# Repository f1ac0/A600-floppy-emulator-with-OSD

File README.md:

# Floppy emulator with OSD and selector for the Amiga 600
This is a fusion of a "Gotek" and a "Bluepill" that can provide both FlashFloppy and FF_OSD and also my Amiga-dual-floppy-selector on a single tiny board that fits inside the Amiga 600, under the original floppy drive. Thank you to Keir Fraser for his firmware https://github.com/keirf/FlashFloppy, and to the chinese people for the original device.

Thanks to the OSD and Amiga keyboard support, LCD/OLED display or buttons are no longer necessary and the device can be almost completely hidden inside Amiga computers, without damaging their case. It is still possible to install a display and buttons, though.

In addition, thanks to "Amiga dual floppy selector" feature, it can daisy-chain between the original floppy drive and the motherboard. In this configuration, the OSD let you choose dynamically which drive is DF0 and DF1. You can enjoy both your original games on floppies and disk images on USB or SDcard !

# Disclaimer
This is a hobbyist project, it comes with no warranty and no support. Also remember that the Amiga machines are about 30 years old and may fail because of such hardware expansions.

This version is not endorsed by the author of FlashFloppy, please don't bother him with issues you might have because of it.

I publish my work under the CC-BY-NC-SA license. The content of this repository is the result of weeks of work, requiring investment in tools, parts, prototypes, and risky tests on his own equipment. For this reason the author does not want third parties to sell products and keep all the profit, usually without even offering support to their customers. If you see people selling this without the consent of the author, don't buy from them.

My modifications to the FF_OSD source are under "the unlicense", like the original code.

If you find it useful and want to reward me : I am always looking for Amiga/Amstrad CPC hardware to repair and hack, please contact me.

# BOM
See iBom.

Other boards you may use with it:
- [A600-1200KeyboardSocket](https://github.com/f1ac0/Breakout-and-simple-connector-boards) to pick the keyboard signals on an A600 or A1200
- [USB_A or microSD breakout](https://github.com/f1ac0/Breakout-and-simple-connector-boards) to make the flash memory accessible from outside the system

# Making it
Components are SMD, and have quite thin pin pitch. You need to know what you are doing.

You may choose to install the USB on a remote board, to make them accessible through trapdoors or openings in the case. You may solder buttons, rotary encoder, LED, display and piezo transducer directly : most "pin headers" pads should not be fitted with headers otherwise it will prevent installing the floppy drive over it.

Solder the bottom floppy pin header at the same angle as the drive is installed in the A600. This way the board should be over the back connectors, and the floppy drive connector will fit tightly under the drive. If any doubt, try to install it before soldering.

Check for shorts at least between 5V, 12V and GND traces before applying power ! If it doesn't work after manual soldering, check that all pads are attached and not shorted, good luck!

The programming ports do not need to be soldered since it needs to be programmed just once : you can just hold it in place during the few seconds required for programming.

On the software side, you need to compile FF\_OSD from source, with the small modifications proposed in the "Floppy-emulator-with-OSD" repository. Use `patch -ru -d FF_OSD-master  < patch` to apply them. FlashFloppy does not require any modification.

To program the F103 uC then the F105 uC, I personally use a STLINK clone dongle with the stlink tool : https://github.com/stlink-org/stlink. Each uC has its own SWDIO/SWDCLK pins.

To connect the wires to DRES, MTRX, CSYNC and VIDEO signals on the A600 motherboard without soldering on it, here is a tip:
- Take a metal pin from the female 2.54mm pin socket, which is shaped as a lyre. The one you removed from pin 3 for example.
- Solder the wire on the pin, where you normally solder it.
- Place the pin inside heat-shrink tube, with only 1mm of metal uncovered from the tips of the lyre.
- Snap the tip on the lyre on the inside of the back connector where you need to connect. DRES, MTRX, CSYNC and VIDEO are easily available on the top row of the video and floppy connectors, which is accessible from inside the case!

# Using it
- Plug the floppy ribbon cable on the device ; connect the DRES and MTRX wires on the rear floppy connector ; plug the device on the motherboard floppy connector ; plug the keyboard adapter on U7 (not U13!) ; connect the VIDEO and CSYNC wires on the video connector ; plug the power connectors to the motherboard and to the drive ; Reinstall the drive over it ; manage the USB connector, for axample in place of the modulator.
- Insert the USB thumb drive.
- Turn on the Amiga, enjoy.

To change the drives configuration :
- First you should eject all floppies to prevent confusion of the OS.
- Go to the FF_OSD config menu, change the Drive config setting accordingly. Then Use or Save the new settings.
- If you changed from one to two or two to one drive, then you need to reboot OS for the second drive to be identified or ignored correctly.

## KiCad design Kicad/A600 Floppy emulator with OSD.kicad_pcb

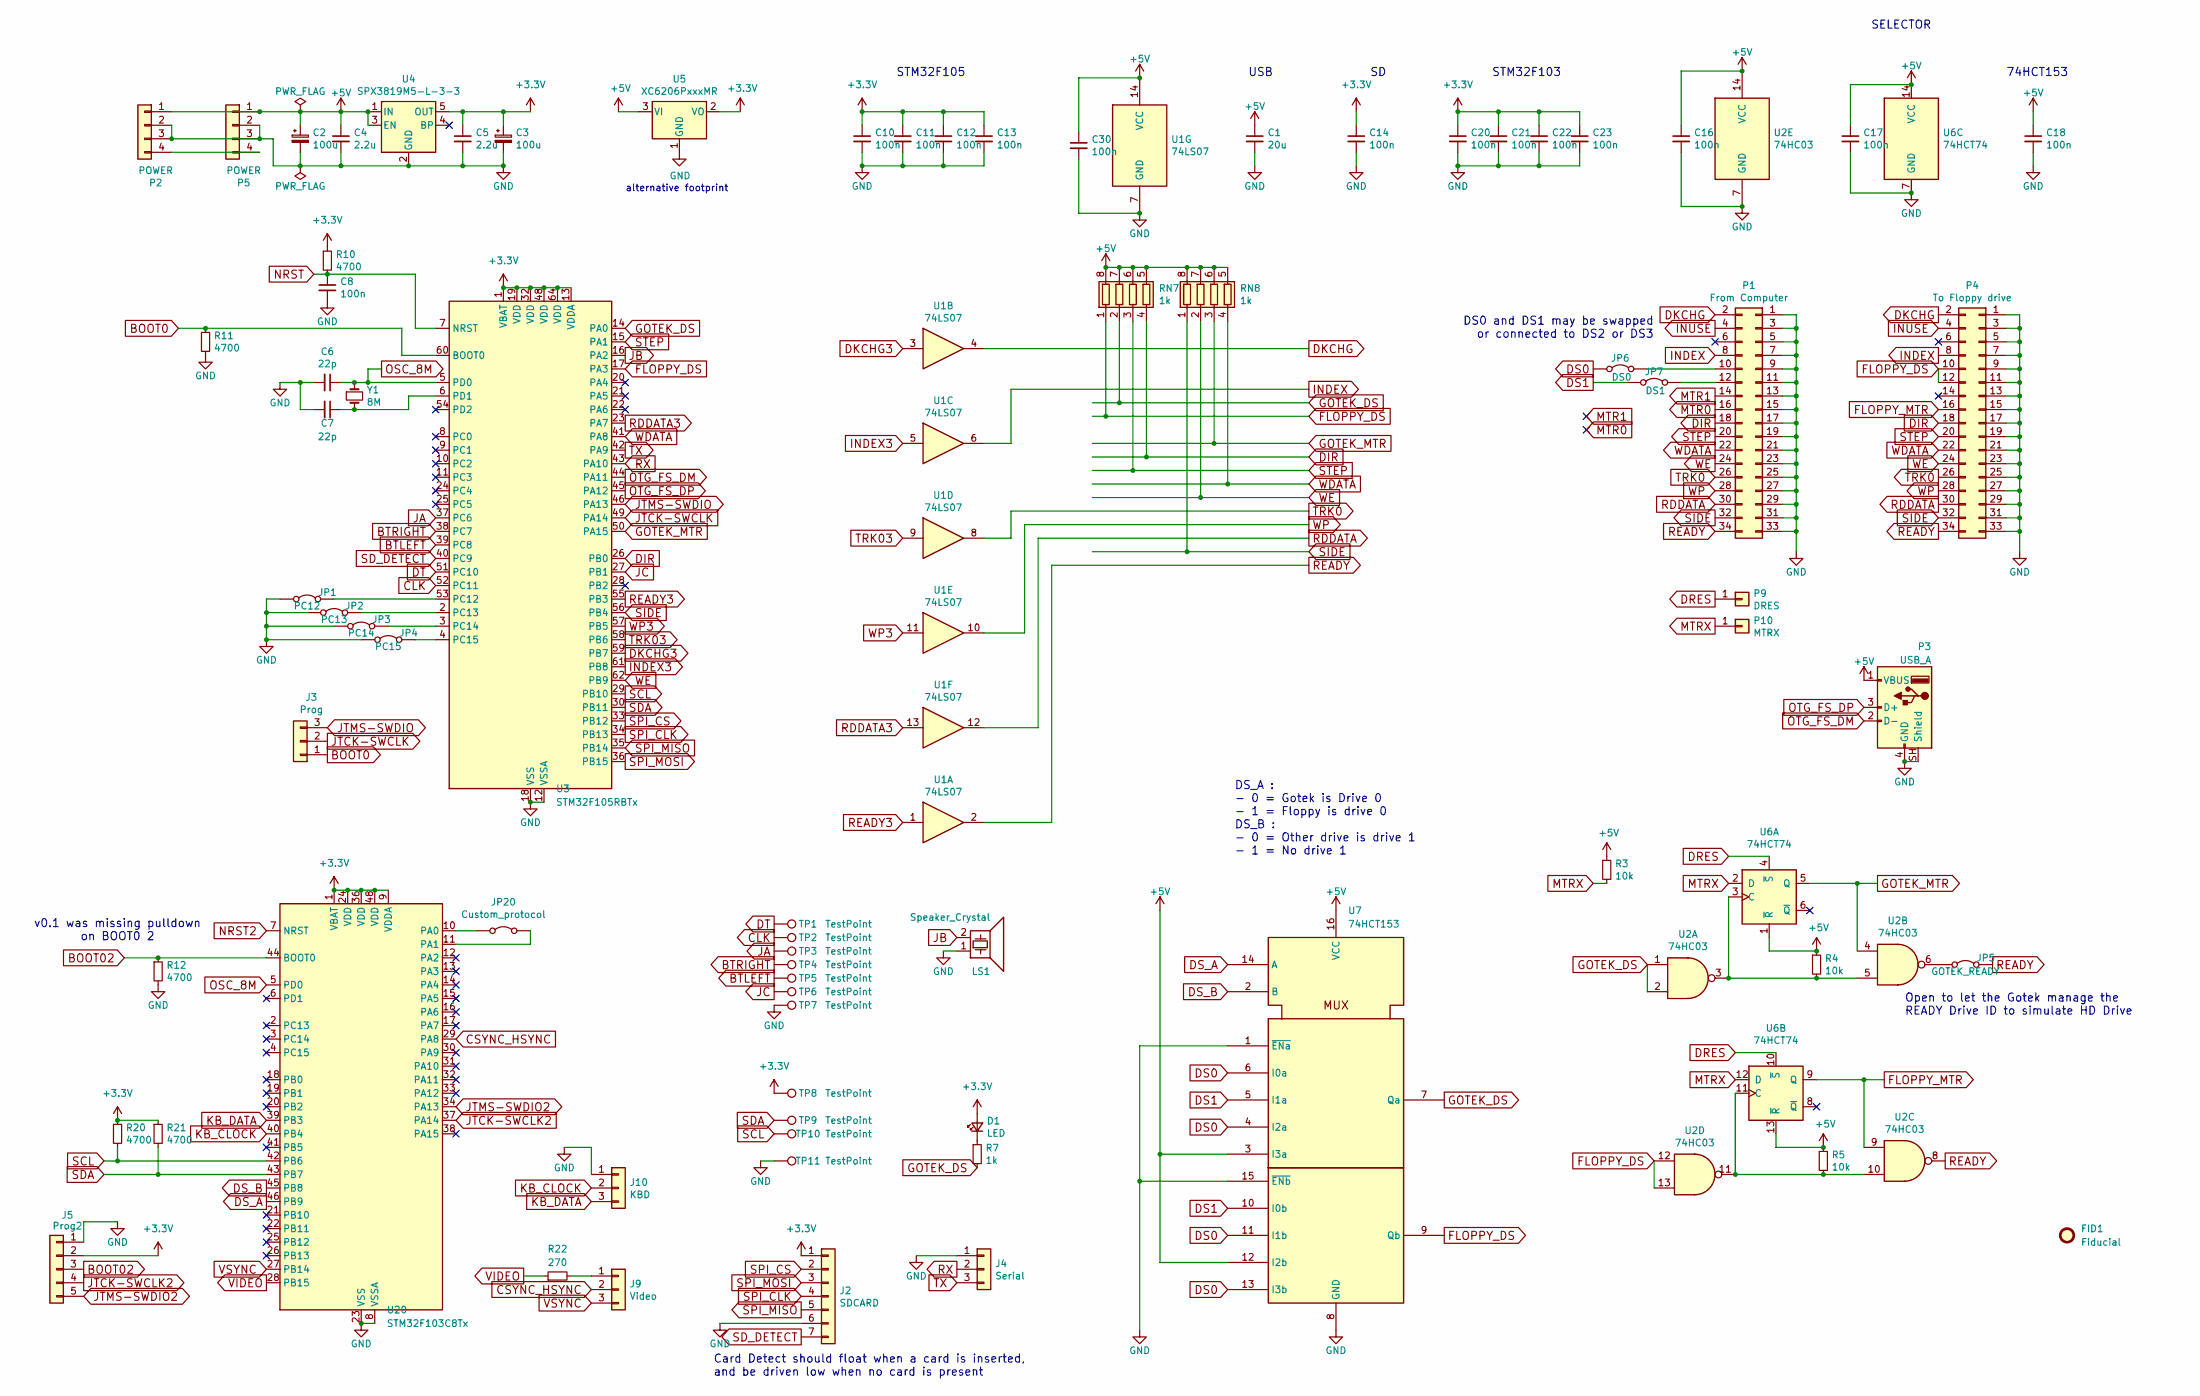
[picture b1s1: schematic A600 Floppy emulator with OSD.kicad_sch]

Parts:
C1: 20u; C_0805_2012Metric
C2, C3: 100u; CP_Radial_D5.0mm_P2.50mm
C4, C5: 2.2u; C_0805_2012Metric
C6, C7: 22p; C_0805_2012Metric
C8, C10, C11, C12, C13, C14, C16, C17, C18, C20, C21, C22, C23, C30: 100n; C_0805_2012Metric
D1: LED; PinHeader_1x02_P2.54mm_Vertical
FID1: Fiducial; CC_BY_NC_SA_long_silkscreen
J2: SDCARD; PinHeader_1x07_P2.54mm_Vertical
J3: Prog; PinHeader_1x03_P2.54mm_Vertical
J4: Serial; PinHeader_1x03_P2.54mm_Vertical
J5: Prog2; PinHeader_1x05_P2.54mm_Vertical
J9: Video; PinHeader_1x03_P2.54mm_Vertical
J10: KBD; PinHeader_1x03_P2.54mm_Vertical
JP1: PC12; SolderJumper-2_P1.3mm_Bridged_RoundedPad1.0x1.5mm
JP2: PC13; SolderJumper-2_P1.3mm_Bridged_RoundedPad1.0x1.5mm
JP3: PC14; SolderJumper-2_P1.3mm_Bridged_RoundedPad1.0x1.5mm
JP4: PC15; SolderJumper-2_P1.3mm_Bridged_RoundedPad1.0x1.5mm
JP5: GOTEK_READY; SolderJumper-2_P1.3mm_Bridged_RoundedPad1.0x1.5mm
JP6: DS0; PinHeader_1x02_P2.54mm_Vertical
JP7: DS1; PinHeader_1x02_P2.54mm_Vertical
JP20: Custom_protocol; SolderJumper-2_P1.3mm_Bridged_RoundedPad1.0x1.5mm
LS1: Speaker_Crystal; PinHeader_1x02_P2.54mm_Vertical
P1: From Computer; PinSocket_2x17_P2.54mm_Vertical
P2: POWER; Floppy_Power_1x04x2.50mm_Horizontal
P3: USB_A; USB_A_female_THT_G54
P4: To Floppy drive; Pin_Header_2x17_Male_EdgeMount_Pitch2.54mm
P5: POWER; Floppy_Power_1x04x2.50mm_Vertical
P9: DRES; PinHeader_1x01_P2.54mm_Vertical
P10: MTRX; PinHeader_1x01_P2.54mm_Vertical
R3, R4, R5: 10k; R_0805_2012Metric
R7: 1k; R_0805_2012Metric
R10, R11, R12, R20, R21: 4700; R_0805_2012Metric
R22: 270; R_0805_2012Metric
RN7, RN8: 1k; R_Array_Convex_4x0603
TP1, TP2, TP3, TP4, TP5, TP6, TP7, TP8, TP9, TP10, TP11: TestPoint; TestPoint_THTPad_D1.7mm_Drill1.0mm
U1: 74LS07; SOIC-14_3.9x8.7mm_P1.27mm
U2: 74HC03; SOIC-14_3.9x8.7mm_P1.27mm
U3: STM32F105RBTx; LQFP-64_10x10mm_P0.5mm
U4: SPX3819M5-L-3-3; SOT-23-5
U5: XC6206PxxxMR; SOT-23
U6: 74HCT74; SOIC-14_3.9x8.7mm_P1.27mm
U7: 74HCT153; SOIC-16_3.9x9.9mm_P1.27mm
U20: STM32F103C8Tx; LQFP-48_7x7mm_P0.5mm
Y1: 8M; Crystal_HC49-4H_Vertical

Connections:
+3.3V: C3.1, C5.1, C10.1, C11.1, C12.1, C13.1, C14.1, C20.1, C21.1, C22.1, C23.1, D1.2 (A), J2.1, J5.2, R10.1, R20.1, R21.1, TP8.1 (1_1), U3.1 (VBAT), U3.13 (VDDA), U3.19 (VDD), U3.32 (VDD), U3.48 (VDD), U3.64 (VDD), U4.5 (OUT), U5.2 (VO), U20.1 (VBAT), U20.9 (VDDA), U20.24 (VDD), U20.36 (VDD), U20.48 (VDD)
+5V: C1.1, C2.1, C4.1, C16.1, C17.1, C18.1, C30.1, P2.1, P3.1 (VBUS), P5.1, R3.1, R4.1, R5.1, RN7.5 (R4.2), RN7.6 (R3.2), RN7.7 (R2.2), RN7.8 (R1.2), RN8.5 (R4.2), RN8.6 (R3.2), RN8.7 (R2.2), RN8.8 (R1.2), U1.14 (VCC), U2.14 (VCC), U4.1 (IN), U4.3 (EN), U5.3 (VI), U6.1 (~R), U6.13 (~R), U6.14 (VCC), U7.3 (I3a), U7.12 (I2b), U7.16 (VCC)
BOOT0: J3.1, R11.1, U3.60 (BOOT0)
BOOT02: J5.3, R12.1, U20.44 (BOOT0)
BTLEFT: TP5.1 (1_1), U3.39 (PC8)
BTRIGHT: TP4.1 (1_1), U3.38 (PC7)
CLK: TP2.1 (1_1), U3.52 (PC11)
CSYNC_HSYNC: J9.2, U20.29 (PA8)
DIR: P1.18, P4.18, RN7.4 (R4.1), U3.26 (PB0)
DKCHG: P1.2, P4.2, U1.4
DKCHG3: U1.3, U3.59 (PB7)
DRES: P9.1 (Pin_1_1), U6.4 (~S), U6.10 (~S)
DS0: JP6.1 (A), U7.4 (I2a), U7.6 (I0a), U7.11 (I1b), U7.13 (I3b)
DS1: JP7.1 (A), U7.5 (I1a), U7.10 (I0b)
DS_A: U7.14 (A), U20.46 (PB9)
DS_B: U7.2 (B), U20.45 (PB8)
DT: TP1.1 (1_1), U3.51 (PC10)
FLOPPY_DS: P4.10, P4.12, RN7.1 (R1.1), U2.12, U2.13, U3.17 (PA3), U7.9 (Qb)
FLOPPY_MTR: P4.16, U2.9, U6.9 (Q)
GND: C1.2, C2.2, C3.2, C4.2, C5.2, C6.2, C7.2, C8.2, C10.2, C11.2, C12.2, C13.2, C14.2, C16.2, C17.2, C18.2, C20.2, C21.2, C22.2, C23.2, C30.2, J2.6, J4.1, J5.1, J10.1, JP1.1 (A), JP2.1 (A), JP3.1 (A), JP4.1 (A), LS1.1, P1.1, P1.3, P1.5, P1.7, P1.9, P1.11, P1.13, P1.15, P1.17, P1.19, P1.21, P1.23, P1.25, P1.27, P1.29, P1.31, P1.33, P2.2, P2.3, P3.4 (GND), P3.SH (Shield), P4.1, P4.3, P4.5, P4.7, P4.9, P4.11, P4.13, P4.15, P4.17, P4.19, P4.21, P4.23, P4.25, P4.27, P4.29, P4.31, P4.33, P5.2, P5.3, R11.2, R12.2, TP7.1 (1_1), TP11.1 (1_1), U1.7 (GND), U2.7 (GND), U3.12 (VSSA), U3.18 (VSS), U3.31 (VSS), U3.47 (VSS), U3.63 (VSS), U4.2 (GND), U5.1 (GND), U6.7 (GND), U7.1 (~ENa), U7.8 (GND), U7.15 (~ENb), U20.8 (VSSA), U20.23 (VSS), U20.35 (VSS), U20.47 (VSS)
GOTEK_DS: R7.2, RN7.2 (R2.1), U2.1, U2.2, U3.14 (PA0), U7.7 (Qa)
GOTEK_MTR: RN8.3 (R3.1), U2.4, U3.50 (PA15), U6.5 (Q)
INDEX: P1.8, P4.8, U1.6
INDEX3: U1.5, U3.61 (PB8)
INUSE: P1.4, P4.4
JA: TP3.1 (1_1), U3.37 (PC6)
JB: LS1.2, U3.16 (PA2)
JC: TP6.1 (1_1), U3.27 (PB1)
JTCK-SWCLK: J3.2, U3.49 (PA14)
JTCK-SWCLK2: J5.4, U20.37 (PA14)
JTMS-SWDIO: J3.3, U3.46 (PA13)
JTMS-SWDIO2: J5.5, U20.34 (PA13)
KB_CLOCK: J10.2, U20.40 (PB4)
KB_DATA: J10.3, U20.39 (PB3)
MTR0: P1.16
MTR1: P1.14
MTRX: P10.1 (Pin_1_1), R3.2, U6.2 (D), U6.12 (D)
NRST: C8.1, R10.2, U3.7 (NRST)
NRST2: U20.7 (NRST)
unnamed: D1.1 (K), R7.1
unnamed: J9.1, R22.2
unnamed: JP1.2 (B), U3.53 (PC12)
unnamed: JP2.2 (B), U3.2 (PC13)
unnamed: JP3.2 (B), U3.3 (PC14)
unnamed: JP4.2 (B), U3.4 (PC15)
unnamed: JP5.1 (A), U2.6
unnamed: JP6.2 (B), P1.10
unnamed: JP7.2 (B), P1.12
unnamed: JP20.1 (A), U20.10 (PA0)
unnamed: JP20.2 (B), U20.11 (PA1)
unnamed: P2.4, P5.4
unnamed: C7.1, U3.6 (PD1), Y1.2
unnamed: R4.2, U2.3, U2.5, U6.3 (C)
unnamed: R5.2, U2.10, U2.11, U6.11 (C)
OSC_8M: C6.1, U3.5 (PD0), U20.5 (PD0), Y1.1
OTG_FS_DM: P3.2 (D-), U3.44 (PA11)
OTG_FS_DP: P3.3 (D+), U3.45 (PA12)
RDDATA: P1.30, P4.30, U1.12
RDDATA3: U1.13, U3.23 (PA7)
READY: JP5.2 (B), P1.34, P4.34, U1.2, U2.8
READY3: U1.1, U3.55 (PB3)
RX: J4.2, U3.43 (PA10)
SCL: R20.2, TP10.1 (1_1), U3.29 (PB10), U20.42 (PB6)
SDA: R21.2, TP9.1 (1_1), U3.30 (PB11), U20.43 (PB7)
SD_DETECT: J2.7, U3.40 (PC9)
SIDE: P1.32, P4.32, RN8.1 (R1.1), U3.56 (PB4)
SPI_CLK: J2.4, U3.34 (PB13)
SPI_CS: J2.2, U3.33 (PB12)
SPI_MISO: J2.5, U3.35 (PB14)
SPI_MOSI: J2.3, U3.36 (PB15)
STEP: P1.20, P4.20, RN7.3 (R3.1), U3.15 (PA1)
TRK0: P1.26, P4.26, U1.8
TRK03: U1.9, U3.58 (PB6)
TX: J4.3, U3.42 (PA9)
VIDEO: R22.1, U20.28 (PB15)
VSYNC: J9.3, U20.27 (PB14)
WDATA: P1.22, P4.22, RN8.4 (R4.1), U3.41 (PA8)
WE: P1.24, P4.24, RN8.2 (R2.1), U3.62 (PB9)
WP: P1.28, P4.28, U1.10
WP3: U1.11, U3.57 (PB5)

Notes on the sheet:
USB
Open to let the Gotek manage the READY Drive ID to simulate HD Drive
v0.1 was missing pulldown on BOOT0 2
Card Detect should float when a card is inserted, and be driven low when no card is present
STM32F103
SELECTOR
74HCT153
alternative footprint
STM32F105
DS0 and DS1 may be swapped or connected to DS2 or DS3
DS_A : - 0 = Gotek is Drive 0 - 1 = Floppy is drive 0 DS_B : - 0 = Other drive is drive 1 - 1 = No drive 1

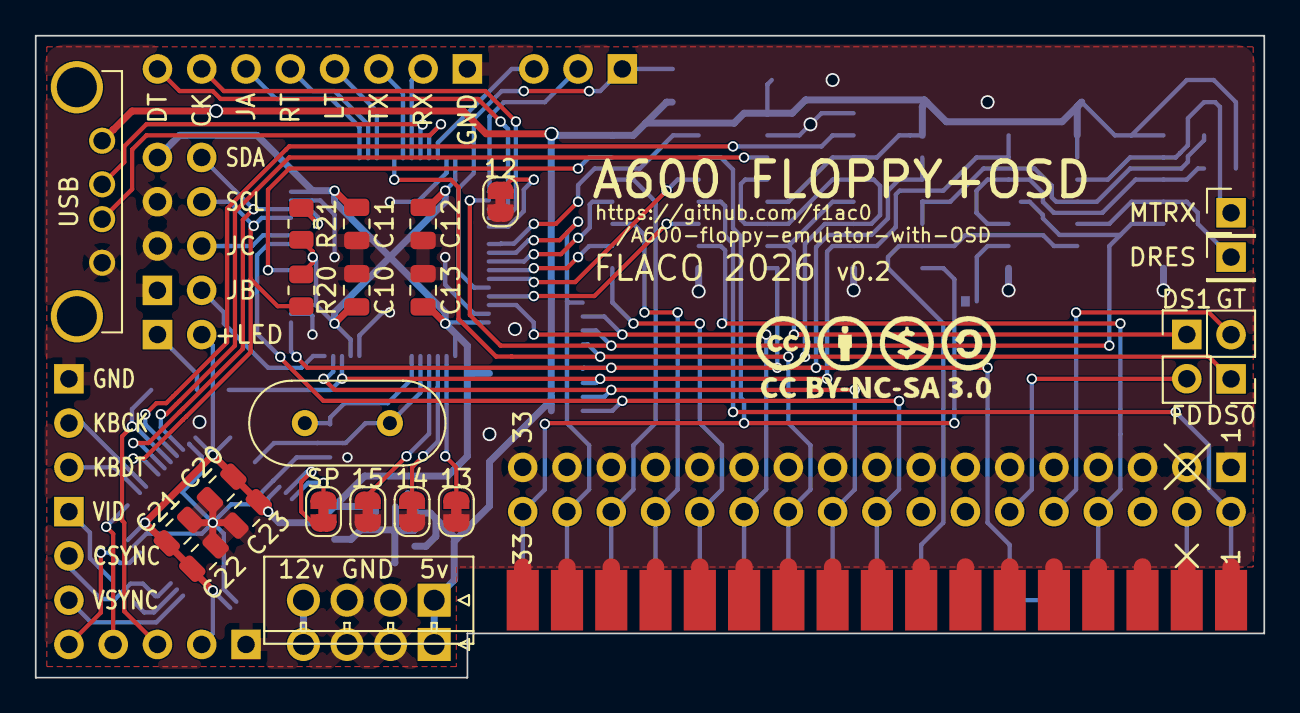
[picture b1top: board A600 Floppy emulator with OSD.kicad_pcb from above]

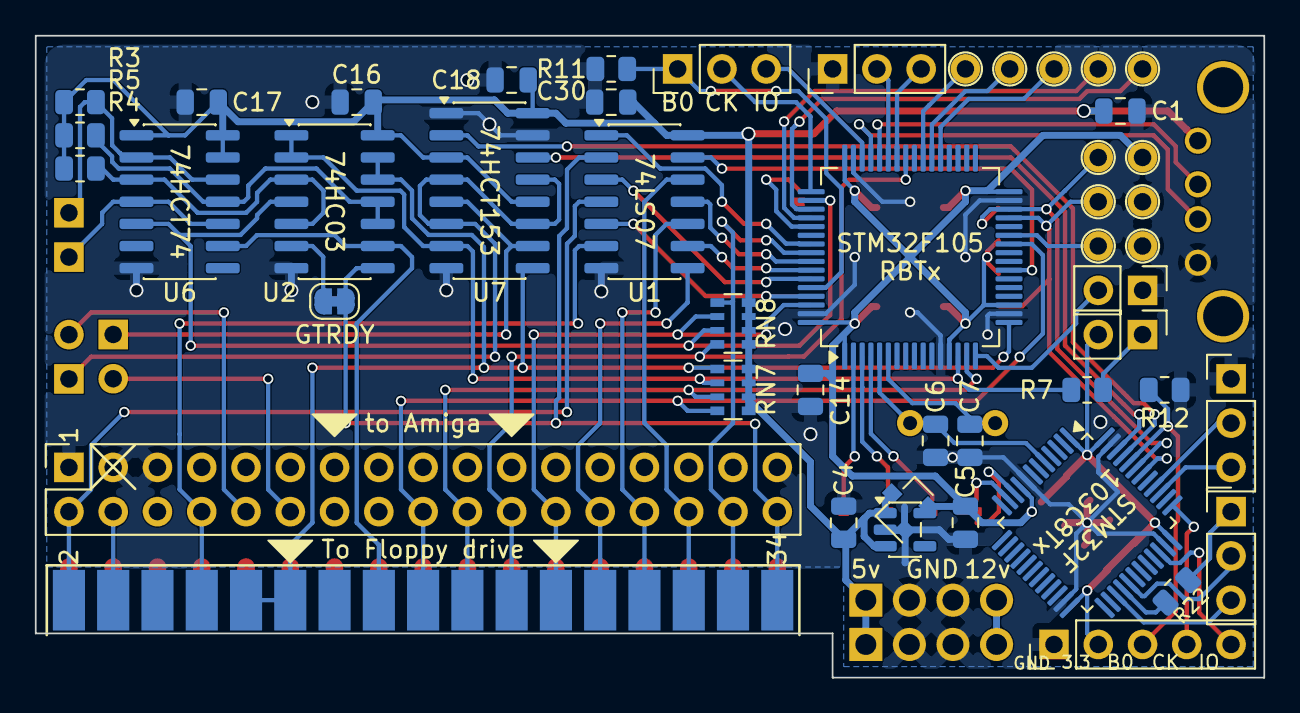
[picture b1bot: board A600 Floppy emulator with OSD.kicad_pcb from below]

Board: 2 copper layers, 70.5 x 36.8 mm, 72 parts (48 on the bottom side), 71 nets.

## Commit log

2026-05-12 Respository init with KiCAD files, Readme and License
2026-05-13 Photo

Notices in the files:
Kicad/A600 Floppy emulator with OSD.kicad_pcb:
FLACO 2020, licence of this PCB is CC-BY-NC-SA
Kicad/A600 Floppy emulator with OSD.kicad_sch:
FLACO 2020, licence of this schematic is CC-BY-NC-SA
